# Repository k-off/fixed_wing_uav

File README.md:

# fixed_wing_uav
A minimal fixed wing drone project

## 3D Model

## ESC board

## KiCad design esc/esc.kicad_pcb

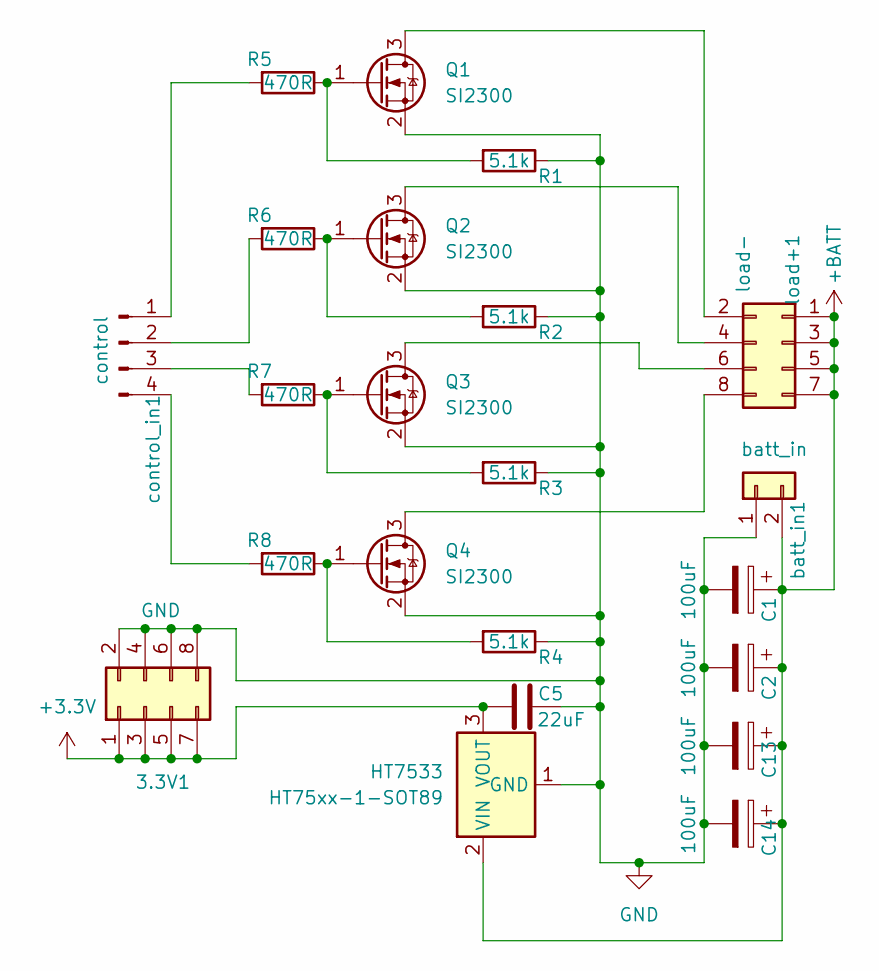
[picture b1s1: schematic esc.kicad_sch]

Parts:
3.3V1: GND; PinSocket_2x04_P2.54mm_Vertical
C1, C2, C13, C14: 100uF; CP_Radial_D10.0mm_P3.50mm
C5: 22uF; C_0805_2012Metric_Pad1.18x1.45mm_HandSolder
HT7533: HT75xx-1-SOT89; SOT-89-3
Q1, Q2, Q3, Q4: SI2300; SOT-23
R1, R2, R3, R4: 5.1k; R_0805_2012Metric_Pad1.20x1.40mm_HandSolder
R5, R6, R7, R8: 470R; R_0805_2012Metric_Pad1.20x1.40mm_HandSolder
batt_in1: batt_in; PinSocket_1x02_P2.54mm_Vertical
control_in1: control; PinSocket_1x04_P2.54mm_Vertical
load+1: load-; PinSocket_2x04_P2.54mm_Vertical

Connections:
+3.3V: 3.3V1.1, 3.3V1.3, 3.3V1.5, 3.3V1.7, C5.1, HT7533.3 (VOUT)
+BATT: C1.1, C2.1, C13.1, C14.1, HT7533.2 (VIN), batt_in1.2, load+1.1, load+1.3, load+1.5, load+1.7
GND: 3.3V1.2, 3.3V1.4, 3.3V1.6, 3.3V1.8, C1.2, C2.2, C5.2, C13.2, C14.2, HT7533.1 (GND), Q1.2 (S), Q2.2 (S), Q3.2 (S), Q4.2 (S), R1.1, R2.1, R3.1, R4.1, batt_in1.1
unnamed: Q1.3 (D), load+1.2
unnamed: Q1.1 (G), R1.2, R5.1
unnamed: Q2.3 (D), load+1.4
unnamed: Q2.1 (G), R2.2, R6.1
unnamed: Q3.3 (D), load+1.6
unnamed: Q3.1 (G), R3.2, R7.1
unnamed: Q4.3 (D), load+1.8
unnamed: Q4.1 (G), R4.2, R8.1
unnamed: R5.2, control_in1.1
unnamed: R6.2, control_in1.2
unnamed: R7.2, control_in1.3
unnamed: R8.2, control_in1.4

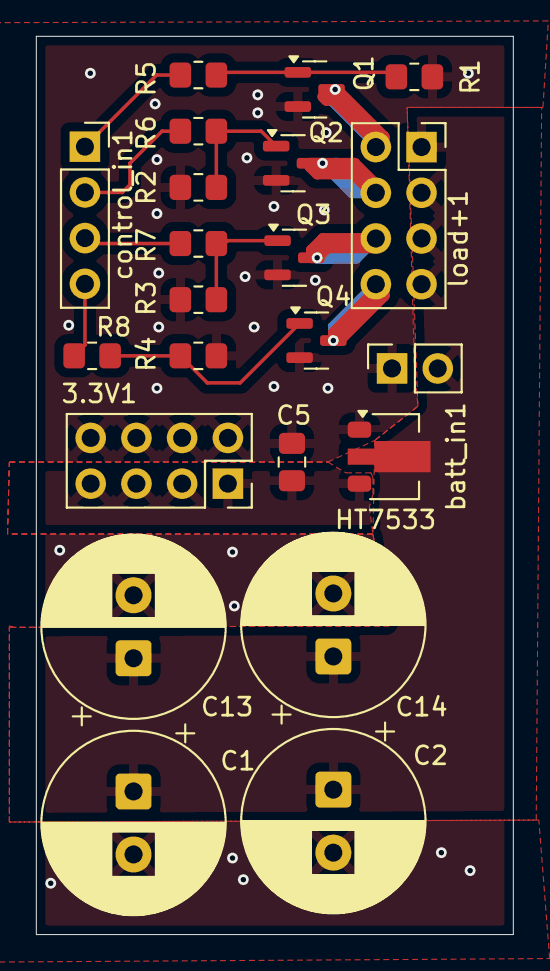
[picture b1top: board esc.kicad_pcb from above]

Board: 2 copper layers, 26.5 x 49.9 mm, 22 parts (0 on the bottom side), 15 nets.

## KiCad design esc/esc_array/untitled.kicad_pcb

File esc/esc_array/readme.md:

JLCPCB manufactures boards of size of up to 100x100mm for the same price.

The esc board is much smaller, so it is possible to combine multiple pcb-s in an array on a single panel.

So here's an array of 6 esc-s.

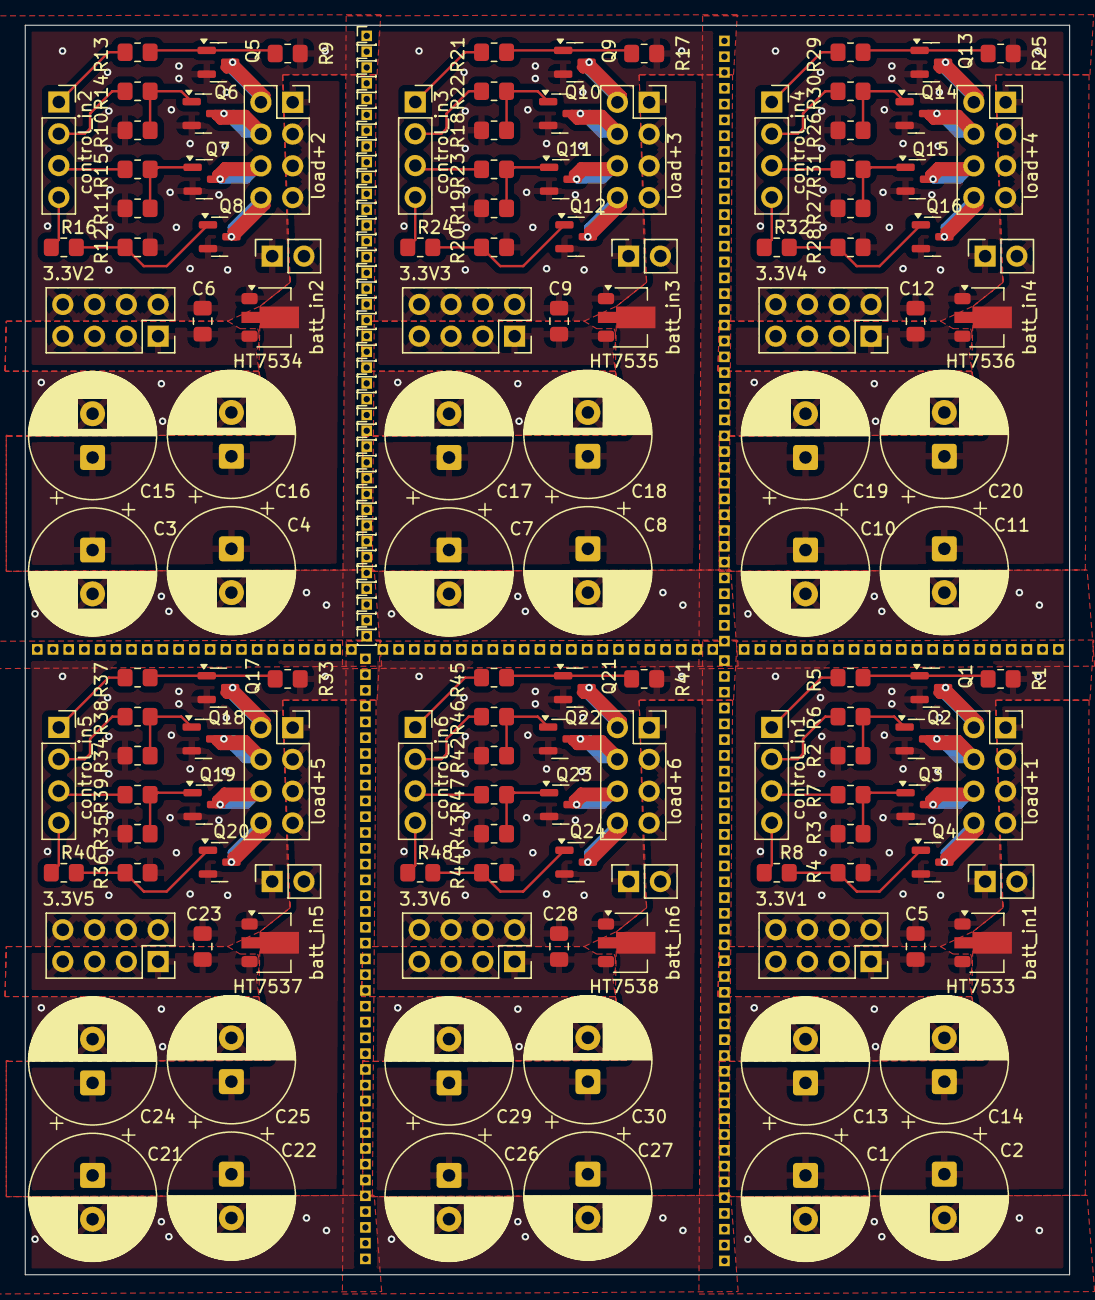
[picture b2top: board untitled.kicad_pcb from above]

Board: 2 copper layers, 83.5 x 99.9 mm, 132 parts (0 on the bottom side), 15 nets.

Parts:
3.3V1, 3.3V2, 3.3V3, 3.3V4, 3.3V5, 3.3V6: GND; PinSocket_2x04_P2.54mm_Vertical
C1, C2, C3, C4, C7, C8, C10, C11, C13, C14, C15, C16, C17, C18, C19, C20, C21, C22, C24, C25, C26, C27, C29, C30: 100uF; CP_Radial_D10.0mm_P3.50mm
C5, C6, C9, C12, C23, C28: 22uF; C_0805_2012Metric_Pad1.18x1.45mm_HandSolder
HT7533, HT7534, HT7535, HT7536, HT7537, HT7538: HT75xx-1-SOT89; SOT-89-3
Q1, Q2, Q3, Q4, Q5, Q6, Q7, Q8, Q9, Q10, Q11, Q12, Q13, Q14, Q15, Q16, Q17, Q18, Q19, Q20, Q21, Q22, Q23, Q24: SI2300; SOT-23
R1, R2, R3, R4, R9, R10, R11, R12, R17, R18, R19, R20, R25, R26, R27, R28, R33, R34, R35, R36, R41, R42, R43, R44: 5.1k; R_0805_2012Metric_Pad1.20x1.40mm_HandSolder
R5, R6, R7, R8, R13, R14, R15, R16, R21, R22, R23, R24, R29, R30, R31, R32, R37, R38, R39, R40, R45, R46, R47, R48: 470R; R_0805_2012Metric_Pad1.20x1.40mm_HandSolder
batt_in1, batt_in2, batt_in3, batt_in4, batt_in5, batt_in6: batt_in; PinSocket_1x02_P2.54mm_Vertical
control_in1, control_in2, control_in3, control_in4, control_in5, control_in6: control; PinSocket_1x04_P2.54mm_Vertical
load+1, load+2, load+3, load+4, load+5, load+6: load-; PinSocket_2x04_P2.54mm_Vertical

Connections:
+3.3V: 3.3V1.1, 3.3V1.3, 3.3V1.5, 3.3V1.7, 3.3V2.1, 3.3V2.3, 3.3V2.5, 3.3V2.7, 3.3V3.1, 3.3V3.3, 3.3V3.5, 3.3V3.7, 3.3V4.1, 3.3V4.3, 3.3V4.5, 3.3V4.7, 3.3V5.1, 3.3V5.3, 3.3V5.5, 3.3V5.7, 3.3V6.1, 3.3V6.3, 3.3V6.5, 3.3V6.7, C5.1, C6.1, C9.1, C12.1, C23.1, C28.1, HT7533.3 (VOUT), HT7534.3 (VOUT), HT7535.3 (VOUT), HT7536.3 (VOUT), HT7537.3 (VOUT), HT7538.3 (VOUT)
+BATT: C1.1, C2.1, C3.1, C4.1, C7.1, C8.1, C10.1, C11.1, C13.1, C14.1, C15.1, C16.1, C17.1, C18.1, C19.1, C20.1, C21.1, C22.1, C24.1, C25.1, C26.1, C27.1, C29.1, C30.1, HT7533.2 (VIN), HT7534.2 (VIN), HT7535.2 (VIN), HT7536.2 (VIN), HT7537.2 (VIN), HT7538.2 (VIN), batt_in1.2, batt_in2.2, batt_in3.2, batt_in4.2, batt_in5.2, batt_in6.2, load+1.1, load+1.3, load+1.5, load+1.7, load+2.1, load+2.3, load+2.5, load+2.7, load+3.1, load+3.3, load+3.5, load+3.7, load+4.1, load+4.3, load+4.5, load+4.7, load+5.1, load+5.3, load+5.5, load+5.7, load+6.1, load+6.3, load+6.5, load+6.7
GND: 3.3V1.2, 3.3V1.4, 3.3V1.6, 3.3V1.8, 3.3V2.2, 3.3V2.4, 3.3V2.6, 3.3V2.8, 3.3V3.2, 3.3V3.4, 3.3V3.6, 3.3V3.8, 3.3V4.2, 3.3V4.4, 3.3V4.6, 3.3V4.8, 3.3V5.2, 3.3V5.4, 3.3V5.6, 3.3V5.8, 3.3V6.2, 3.3V6.4, 3.3V6.6, 3.3V6.8, C1.2, C2.2, C3.2, C4.2, C5.2, C6.2, C7.2, C8.2, C9.2, C10.2, C11.2, C12.2, C13.2, C14.2, C15.2, C16.2, C17.2, C18.2, C19.2, C20.2, C21.2, C22.2, C23.2, C24.2, C25.2, C26.2, C27.2, C28.2, C29.2, C30.2, HT7533.1 (GND), HT7534.1 (GND), HT7535.1 (GND), HT7536.1 (GND), HT7537.1 (GND), HT7538.1 (GND), Q1.2 (S), Q2.2 (S), Q3.2 (S), Q4.2 (S), Q5.2 (S), Q6.2 (S), Q7.2 (S), Q8.2 (S), Q9.2 (S), Q10.2 (S), Q11.2 (S), Q12.2 (S), Q13.2 (S), Q14.2 (S), Q15.2 (S), Q16.2 (S), Q17.2 (S), Q18.2 (S), Q19.2 (S), Q20.2 (S), Q21.2 (S), Q22.2 (S), Q23.2 (S), Q24.2 (S), R1.1, R2.1, R3.1, R4.1, R9.1, R10.1, R11.1, R12.1, R17.1, R18.1, R19.1, R20.1, R25.1, R26.1, R27.1, R28.1, R33.1, R34.1, R35.1, R36.1, R41.1, R42.1, R43.1, R44.1, batt_in1.1, batt_in2.1, batt_in3.1, batt_in4.1, batt_in5.1, batt_in6.1
unnamed: Q1.3 (D), Q5.3 (D), Q9.3 (D), Q13.3 (D), Q17.3 (D), Q21.3 (D), load+1.2, load+2.2, load+3.2, load+4.2, load+5.2, load+6.2
unnamed: Q1.1 (G), Q5.1 (G), Q9.1 (G), Q13.1 (G), Q17.1 (G), Q21.1 (G), R1.2, R5.1, R9.2, R13.1, R17.2, R21.1, R25.2, R29.1, R33.2, R37.1, R41.2, R45.1
unnamed: Q2.3 (D), Q6.3 (D), Q10.3 (D), Q14.3 (D), Q18.3 (D), Q22.3 (D), load+1.4, load+2.4, load+3.4, load+4.4, load+5.4, load+6.4
unnamed: Q2.1 (G), Q6.1 (G), Q10.1 (G), Q14.1 (G), Q18.1 (G), Q22.1 (G), R2.2, R6.1, R10.2, R14.1, R18.2, R22.1, R26.2, R30.1, R34.2, R38.1, R42.2, R46.1
unnamed: Q3.3 (D), Q7.3 (D), Q11.3 (D), Q15.3 (D), Q19.3 (D), Q23.3 (D), load+1.6, load+2.6, load+3.6, load+4.6, load+5.6, load+6.6
unnamed: Q3.1 (G), Q7.1 (G), Q11.1 (G), Q15.1 (G), Q19.1 (G), Q23.1 (G), R3.2, R7.1, R11.2, R15.1, R19.2, R23.1, R27.2, R31.1, R35.2, R39.1, R43.2, R47.1
unnamed: Q4.3 (D), Q8.3 (D), Q12.3 (D), Q16.3 (D), Q20.3 (D), Q24.3 (D), load+1.8, load+2.8, load+3.8, load+4.8, load+5.8, load+6.8
unnamed: Q4.1 (G), Q8.1 (G), Q12.1 (G), Q16.1 (G), Q20.1 (G), Q24.1 (G), R4.2, R8.1, R12.2, R16.1, R20.2, R24.1, R28.2, R32.1, R36.2, R40.1, R44.2, R48.1
unnamed: R5.2, R13.2, R21.2, R29.2, R37.2, R45.2, control_in1.1, control_in2.1, control_in3.1, control_in4.1, control_in5.1, control_in6.1
unnamed: R6.2, R14.2, R22.2, R30.2, R38.2, R46.2, control_in1.2, control_in2.2, control_in3.2, control_in4.2, control_in5.2, control_in6.2
unnamed: R7.2, R15.2, R23.2, R31.2, R39.2, R47.2, control_in1.3, control_in2.3, control_in3.3, control_in4.3, control_in5.3, control_in6.3
unnamed: R8.2, R16.2, R24.2, R32.2, R40.2, R48.2, control_in1.4, control_in2.4, control_in3.4, control_in4.4, control_in5.4, control_in6.4

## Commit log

2025-07-17 esc v0.1
2025-07-17 add common header
2025-07-17 add controller sketch
2025-07-17 add vehicle sketch
2025-07-18 add resources
2025-07-18 add 3d model v0.1
2025-07-18 add XTEA packet encryption, not tested
